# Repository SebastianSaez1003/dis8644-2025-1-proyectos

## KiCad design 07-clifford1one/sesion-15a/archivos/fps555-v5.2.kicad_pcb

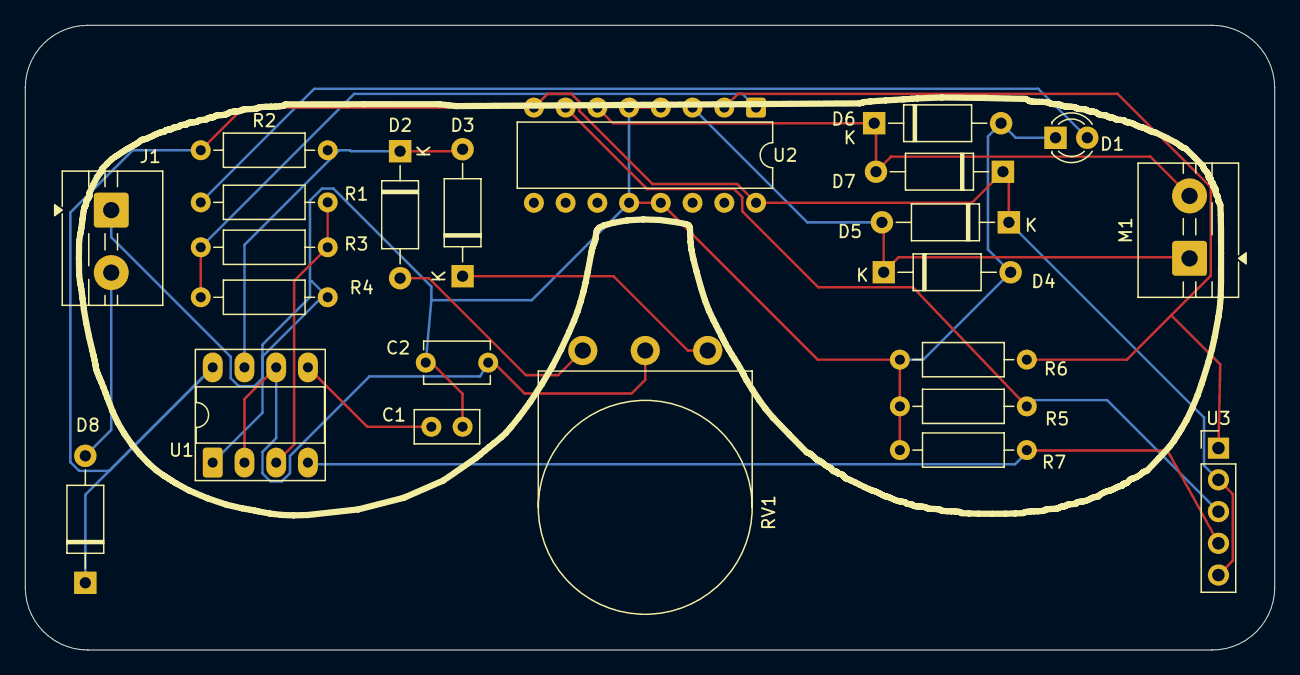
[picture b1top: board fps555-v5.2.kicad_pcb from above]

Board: 2 copper layers, 100.0 x 50.0 mm, 23 parts (0 on the bottom side), 16 nets.

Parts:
C1: 100n; C_Disc_D5.0mm_W2.5mm_P2.50mm
C2: 470p; C_Disc_D5.1mm_W3.2mm_P5.00mm
D1: LED; LED_D3.0mm_Clear
D2, D3, D4, D5, D6, D7, D8: 4007; D_A-405_P10.16mm_Horizontal
J1: Batería 9v; TerminalBlock_MaiXu_MX126-5.0-02P_1x02_P5.00mm
M1: Motorreductor; TerminalBlock_MaiXu_MX126-5.0-02P_1x02_P5.00mm
R1, R3: 1k; R_Axial_DIN0207_L6.3mm_D2.5mm_P10.16mm_Horizontal
R2: 10k; R_Axial_DIN0207_L6.3mm_D2.5mm_P10.16mm_Horizontal
R4, R7: 100k; R_Axial_DIN0207_L6.3mm_D2.5mm_P10.16mm_Horizontal
R5, R6: 470k; R_Axial_DIN0207_L6.3mm_D2.5mm_P10.16mm_Horizontal
RV1: 500k; Potentiometer_Omeg_PC16BU_Vertical
U1: 555; DIP-8_W7.62mm_Socket_LongPads
U2: L293D; DIP-16_W7.62mm
U3: mst303; PinHeader_1x05_P2.54mm_Vertical

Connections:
+9V: D8.2 (A), J1.2
GND: C1.2, C2.2, D1.1 (K), D4.2 (A), D6.2 (A), J1.1, R4.2, R5.1, R6.1, R7.1, U1.1 (GND), U2.4 (GND), U2.5 (GND), U2.12 (GND), U2.13 (GND)
unnamed: D1.2 (A), R1.2
unnamed: D2.2 (A), RV1.1
unnamed: D2.1 (K), D3.2 (A), R2.2, U1.7 (DIS)
unnamed: D3.1 (K), RV1.3
unnamed: D4.1 (K), D5.2 (A), M1.1 (+), U2.3 (1Y)
unnamed: D6.1 (K), D7.2 (A), M1.2 (-), U2.6 (2Y)
unnamed: C1.1, U1.5 (CV)
unnamed: R1.1, R3.1, U1.3 (Q)
unnamed: R7.2, U1.4 (R), U3.4
unnamed: C2.1, RV1.2, U1.2 (TR), U1.6 (THR)
unnamed: R6.2, U2.2 (1A), U3.1
unnamed: R5.2, U2.7 (2A), U3.3
unnamed: R3.2, R4.1, U2.1 (EN1,2)
VCC: D5.1 (K), D7.1 (K), D8.1 (K), R2.1, U1.8 (VCC), U2.8 (VCC2), U2.16 (VCC1), U3.2, U3.5

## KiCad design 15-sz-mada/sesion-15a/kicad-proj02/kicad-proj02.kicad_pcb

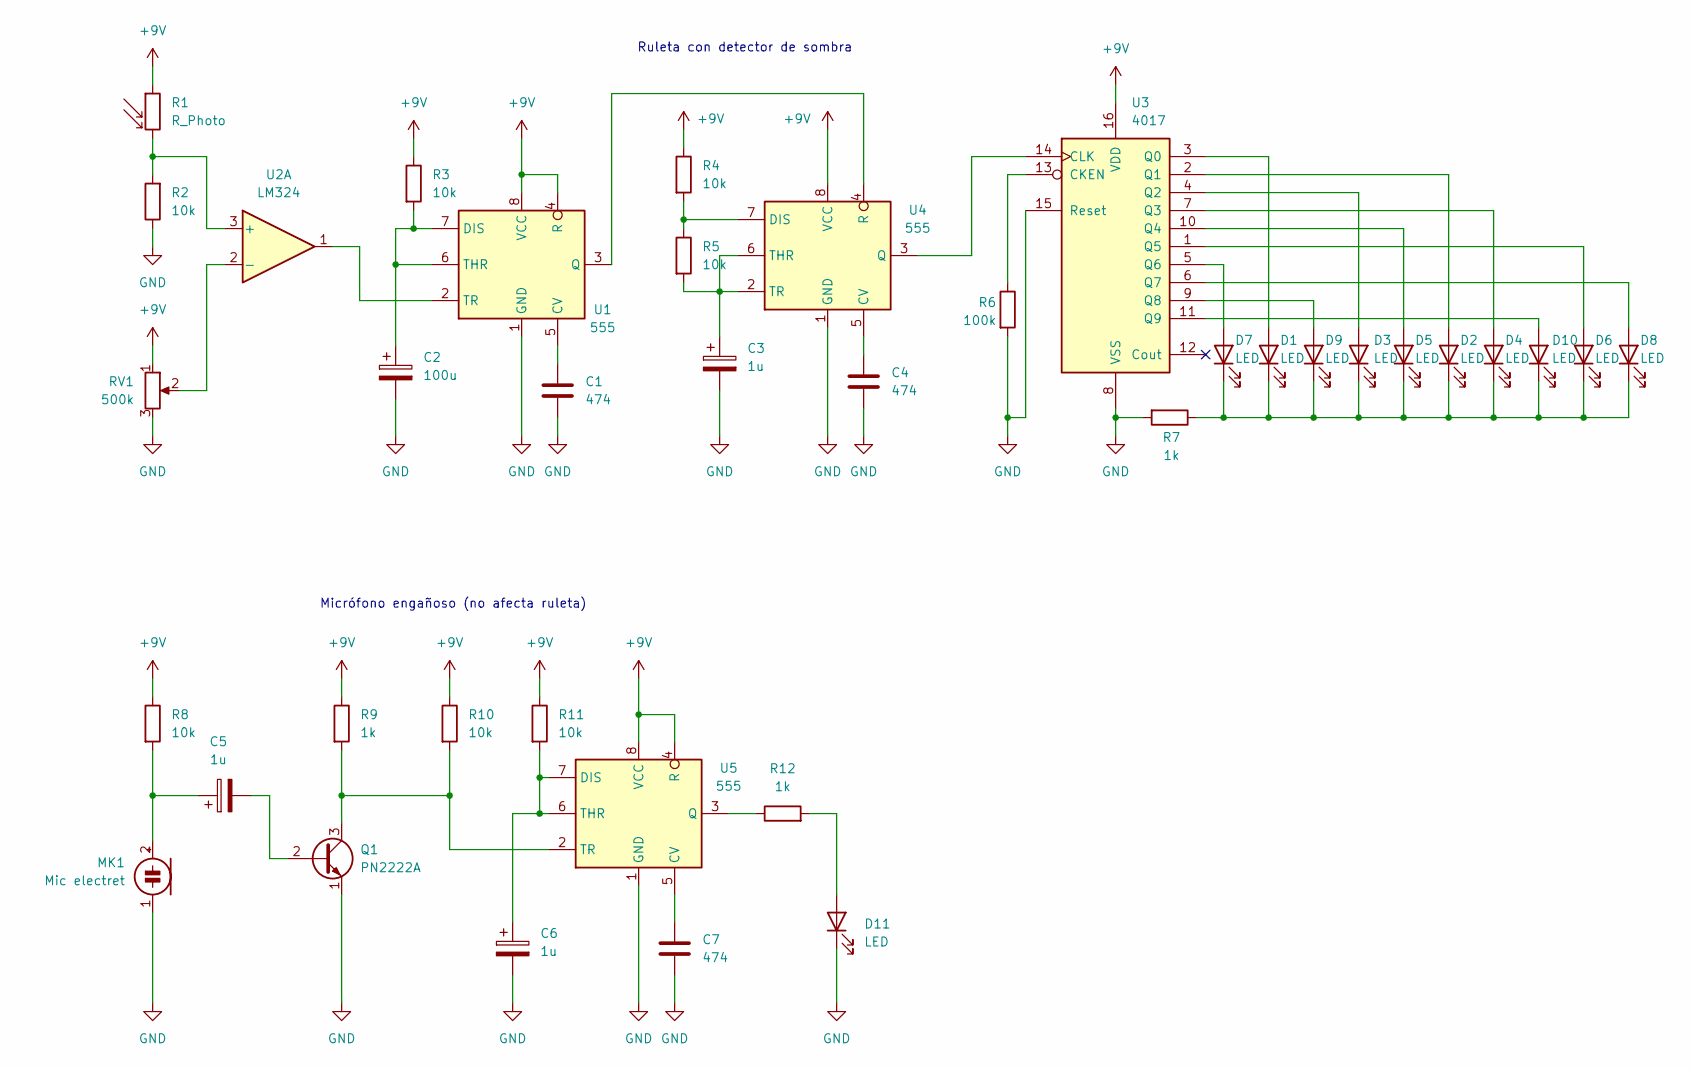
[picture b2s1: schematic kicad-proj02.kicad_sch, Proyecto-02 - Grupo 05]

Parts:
C1, C4, C7: 474; C_Disc_D5.0mm_W2.5mm_P5.00mm
C2: 100u; CP_Radial_D6.3mm_P2.50mm
C3, C5, C6: 1u; CP_Radial_D6.3mm_P2.50mm
D1, D2, D3, D4, D5, D6, D7, D8, D9, D10, D11: LED; LED_D5.0mm
MK1: Mic electret; POM-2244P-C3310-2-R
Q1: PN2222A; TO-92_Inline
R1: R_Photo; R_LDR_5.1x4.3mm_P3.4mm_Vertical
R2, R3, R4, R5, R8, R10, R11: 10k; R_Axial_DIN0207_L6.3mm_D2.5mm_P10.16mm_Horizontal
R6: 100k; R_Axial_DIN0207_L6.3mm_D2.5mm_P10.16mm_Horizontal
R7, R9, R12: 1k; R_Axial_DIN0207_L6.3mm_D2.5mm_P10.16mm_Horizontal
RV1: 500k; Potentiometer_Piher_T-16H_Single_Horizontal
U1, U4, U5: 555; DIP-8_W7.62mm_Socket_LongPads
U2: LM324; DIP-14_W7.62mm_Socket_LongPads
U3: 4017; DIP-16_W7.62mm_Socket_LongPads

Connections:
+9V: R1.1, R3.1, R4.1, R8.1, R9.1, R10.1, R11.1, RV1.1, U1.4 (R), U1.8 (VCC), U3.16 (VDD), U4.8 (VCC), U5.4 (R), U5.8 (VCC)
GND: C1.2, C2.2, C3.2, C4.2, C6.2, C7.2, D11.1 (K), MK1.1 (-), Q1.1 (E), R2.1, R6.2, R7.2, RV1.3, U1.1 (GND), U3.8 (VSS), U3.15 (Reset), U4.1 (GND), U5.1 (GND)
unnamed: D1.2 (A), U3.3 (Q0)
unnamed: D1.1 (K), D2.1 (K), D3.1 (K), D4.1 (K), D5.1 (K), D6.1 (K), D7.1 (K), D8.1 (K), D9.1 (K), D10.1 (K), R7.1
unnamed: D2.2 (A), U3.2 (Q1)
unnamed: D3.2 (A), U3.4 (Q2)
unnamed: D4.2 (A), U3.7 (Q3)
unnamed: D5.2 (A), U3.10 (Q4)
unnamed: D6.2 (A), U3.1 (Q5)
unnamed: D7.2 (A), U3.5 (Q6)
unnamed: D8.2 (A), U3.6 (Q7)
unnamed: D9.2 (A), U3.9 (Q8)
unnamed: D10.2 (A), U3.11 (Q9)
unnamed: D11.2 (A), R12.2
unnamed: C5.1, MK1.2 (+), R8.2
unnamed: C5.2, Q1.2 (B)
unnamed: Q1.3 (C), R9.2, R10.2, U5.2 (TR)
unnamed: C1.1, U1.5 (CV)
unnamed: C2.1, R3.2, U1.6 (THR), U1.7 (DIS)
unnamed: U1.3 (Q), U4.4 (R)
unnamed: U1.2 (TR), U2.1
unnamed: R1.2, R2.2, U2.3 (+)
unnamed: RV1.2, U2.2 (-)
unnamed: R6.1, U3.13 (CKEN)
unnamed: U3.14 (CLK), U4.3 (Q)
unnamed: C4.1, U4.5 (CV)
unnamed: R4.2, R5.1, U4.7 (DIS)
unnamed: C3.1, R5.2, U4.2 (TR), U4.6 (THR)
unnamed: C7.1, U5.5 (CV)
unnamed: C6.1, R11.2, U5.6 (THR), U5.7 (DIS)
unnamed: R12.1, U5.3 (Q)

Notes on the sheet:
Micrófono engañoso (no afecta ruleta)
Ruleta con detector de sombra

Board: 2 copper layers, 38 parts (0 on the bottom side), 31 nets, no tracks yet.
